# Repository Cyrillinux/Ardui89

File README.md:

#Ardui89 8051 C IDE 0.4.2 for Arduino IDE

#Under GPL license

Adds 8051 architecture family to the Arduino IDE :
STC89C52RC, STC89C516RD+, STC15W408AS-DIP16

* DISCLAIMER OF ALL WARRANTIES *

Allows you to COMPILE a .ino file of the 8051 C family program and UPLOAD it into the STC89C5x, STC15..., etc. family.

#Versions
0.0.1  : first Mac OS try (compiling only) (Arch 8051 STC89C51RC(4kb) and STC89C52RC(8kb))
0.0.6   : Mac OS completed (compiling and programming)
0.1.1   : tone function builtin, bugs fixed
0.2.0   : first windows try (compilling only)
0.2.1   : fist windows version completed (compilling and programming)
0.2.2   : Warning : new PINOUT for 805x Arduino equivalent and add STC32G12K128 = 8952 with 128k flash memory
0.2.3   : PINOUT fixed, bugs fixed. Variants STC15F2K32S2, STC32G12K128 fixed
0.3.0   : Replace stcflash by stcgal -> stc15 best process, add STC15W408AS-DIP16
0.3.1   : Bugs fixed
0.3.2   : Mini bugs fixed. Primary linux beta version ready : See dependencies packages installation.
0.3.3   : Mini bugs fixed. Speed uplaod bug fixed / choice speed upload menu added
0.3.7   : Add Serial.readString / Add push-pull output configuration for STC micro-controllers
0.3.8   : (25/04/25) Ardui89 Cinque-Uno replaced by Uno 5X, any bugs fixed
0.3.9   : (25/05/23) Any bugs fixed : compiling core problem on Mac OS Sequoia and Windows 11
0.3.10  : (25/05/27) Add int_to_string like function (same to_string but for int exclusively), and 8051/pgmspace.h 
0.3.11  : (25/05/31) add STC89C516RD+ (62464 bytes (64kb-internal isp)) and 22.1184 Mhz clock option
BETA 0.3.12 : (25/06/14) add #include <string.h> + Prévoir les STC15F2K16 et K32 et STC32G12k128.
0.4.0   : (25/07/27) better RAM management
0.4.1   : (25/10/16) add 29.4912 Mhz external and internal clock option
0.4.1.1 : (26/03/08) same 0.4.1, just UNO Cinque X Board Revision (R2)
0.4.2   : (26/05/16) analogRead and analogPin functions add for STC15 / pwd/tone compute modifed, based on F_CPU (not only 11059200Mhz) / new programme size compute.
    analogPin(A0) or pinMode(A0,INPUT_ANALOG) / analogRead(A0)

#Platforms
MacOS, Wind'Oz. (Stable)

#To do
analogRead, analogWrite with ST15 and ST32 series.
Stable Linux version.

#Installation and test

1/ Donwload Arduino >= V1.8.19 

2/ Launch Arduino

3/ In Arduino->Preferences->Additional Board Manager URLS
    add for Arduino All Versions
    https://master.dl.sourceforge.net/project/stc89/packages/package_ardui89_index.json?viasf=1
    
4/ In Tools->Boards:...->Board Manager
    search "8051"
    select and install "ardui89 8051 family Boards"
    
5/ In Tools->Board:...
    select "Board : "STC89C52RC" "STC89C516RD+" "STC15W408AS-DIP16""
    
6/ Demos :
    Use Blink.ino in basics examples or in Ardui89_demos path :
    Hello.ino
    Howareyou.ino
    
    and build and upload !

#Linux Dependencies

python3 / python3-pip / stcgal / sdcc

Under terminal :

1/ Installing stcgal :

sudo apt-get install python3 python3-pip

sudo python3 -m pip stcgal

2/ Installing SDCC :

sudo apt-get install sdcc

#Important

Under Wind'Oz, using absoluty last version (>=3.8) of CH340 drivers (CH341SER.ZIP) (Included in this package).

Many thanks

Cyril BARBATO

https://sourceforge.net/projects/stc89
cyril.barbato@gmx.com

# Arduino <=> STC89C51/STC89C52/STC89C5x/STC89C51x pinout equivalent
(Ardui89 Cinque Uno/Due/128k R0)

D : Arduino digital pins
A : Arduino analog pins
LED_BULTIN : D13 (P3.5)

 D                                                                 D  A
               +---------------\/--------------+
               |                               |
 7 P1.0 -------|  1  P1.0              VCC  40 |------ VCC
 8 P1.1 -------|  2  P1.1             P0.0  39 |------ P0.0 (AD0) 31 A7
 2 P1.2 -------|  3  P1.2             P0.1  38 |------ P0.1 (AD1) 30 A6
 3 P1.3 -------|  4  P1.3             P0.2  37 |------ P0.2 (AD2) 29 A5 SCL
 4 P1.4 -------|  5  P1.4             P0.3  36 |------ P0.3 (AD3) 28 A4 SDA
 5 P1.5 (MOSI)-|  6  P1.5 (MOSI)      P0.4  35 |------ P0.4 (AD4) 27 A3
 6 P1.6 (MISO)-|  7  P1.6 (MISO)      P0.5  34 |------ P0.5 (AD5) 26 A2
 7 P1.7 (SCK)--|  8  P1.7 (SCK)       P0.6  33 |------ P0.6 (AD6) 25 A1
    RST -------|  9  RST              P0.7  32 |------ P0.7 (AD7) 24 A0
 0 P3.0 -------| 10  P3.0 (RXD)   (VPP) EA  31 |------ EA   (VPP)
 1 P3.1 -------| 11  P3.1 (TXD)  (PRG) ALE  30 |------ ALE  (PRG)
10 P3.2 -------| 12  P3.2 (INT0)     /PSEN  29 |------ /PSEN
11 P3.3 -------| 13  P3.3 (INT1)      P2.7  28 |------ P2.7 (A15) 23
12 P3.4 -------| 14  P3.4 (T0)        P2.6  27 |------ P2.6 (A14) 22
13 P3.5 -------| 15  P3.5 (T1)        P2.5  26 |------ P2.5 (A13) 21
14 P3.6 -------| 16  P3.6 (WR)        P2.4  25 |------ P2.4 (A12) 20
15 P3.7 -------| 17  P3.7 (RD)        P2.3  24 |------ P2.3 (A11) 19
  XTAL2 -------| 18  XTAL2            P2.2  23 |------ P2.2 (A10) 18
  XTAL1 -------| 19  XTAL1 P          P2.1  22 |------ P2.1 (A9)  17
    GND -------| 20  GND              P2.0  21 |------ P2.0 (A8)  16
               +-------------------------------+

# Arduino <=> STC15W408AS-DIP28 / STC15F2K16 or 32 pinout equivalent
(Ardui89 UNO R0)

D : Arduino digital pins
A : Arduino analog pins
LED_BULTIN : D13 (P2.5)
SDA : A4 (D22/P1.4)
SCL : A5 (D23/P1.5)

A   D                                                                         D
                  +---------------------\_/--------------------+
   14 P2.6 -------|  1 P2.6 (CCP1)            (CCP0_3) P2.5 28 |------- P2.5 13
   15 P2.7 -------|  2 P2.7 (CCP2)             (ECI_3) P2.4 27 |------- P2.4 12
A0 18 P1.0 -------|  3 P1.0 (RxD2)            (MOSI_2) P2.3 26 |------- P2.3 11
A1 19 P1.1 -------|  4 P1.1 (TxD2)            (MISO_2) P2.2 25 |------- P2.2 10
A2 20 P1.2 -------|  5 P1.2 (ECI)             (SCLK_2) P2.1 24 |------- P2.1  9
A3 21 P1.3 -------|  6 P1.3 (MOSI)        (RSTOUT_LOW) P2.0 23 |------- P2.0  8
A4 22 P1.4 -------|  7 P1.4 (MISO) (INT3/TxD_2/CCP2_2) P3.7 22 |------- P3.7  7
A5 23 P1.5 -------|  8 P1.5 (SCLK)  (NT2/RxD_2/CCP1_2) P3.6 21 |------- P3.6  6
       XT2 -------|  9 P1.6 (XTAL2) (T1/T0CLKO/CCP0_2) P3.5 20 |------- P3.5  5
       XT1 -------| 10 P1.7 (XTAL1)  (T0/T1CLKO/ECI_2) P3.4 19 |------- P3.4  4
   16  RST -------| 11 P5.4 (MCLKO)             (INT1) P3.3 18 |------- P3.3  3
       Vcc -------| 12 Vcc                      (INT0) P3.2 17 |------- P3.2  2
   17 P5.5 -------| 13 P5.5                   (TxD/T2) P3.1 16 |------- P3.1  1
      Gnd  -------| 14  Gnd          (RxD/INT4/T2CLKO) P3.0 15 |------- P3.0  0
                  +--------------------------------------------+

# Arduino <=> STC15W408AS-DIP16
(Ardui89 MINI R0)

D : Arduino digital pins
A : Arduino analog pins
LED_BULTIN : D7 (P3.7)
SDA : A4 (D12/P1.4)
SCL : A5 (D13/P1.5)

 D   A                                                                 A D
                   +-----------------\_/----------------+
 10 A2 P1.2 -------| 1 P1.2                     P1.1 16 |------- P1.1 A1 9
 11 A3 P1.3 -------| 2 P1.3 (MOSI)              P1.0 15 |------- P1.0 A0 8
 12 A4 P1.4 -------| 3 P1.4 (MISO) (/INT3-TxD2) P3.7 14 |------- P3.7    7
 13 A5 P1.5 -------| 4 P1.5 (SLK)  (/INT2-RxD2) P3.6 13 |------- P3.6    6
  4    P5.4 -------| 5 P5.4              (INT1) P3.3 12 |------- P3.3    3
        Vcc -------| 6 Vcc               (INT0) P3.2 11 |------- P3.2    2
  5    P5.5 -------| 7 P5.5               (TxD) P3.1 10 |------- P3.1    1
        Gnd -------| 8 Gnd                (RxD) P3.0  9 |------- P3.0    0
                   +------------------------------------+

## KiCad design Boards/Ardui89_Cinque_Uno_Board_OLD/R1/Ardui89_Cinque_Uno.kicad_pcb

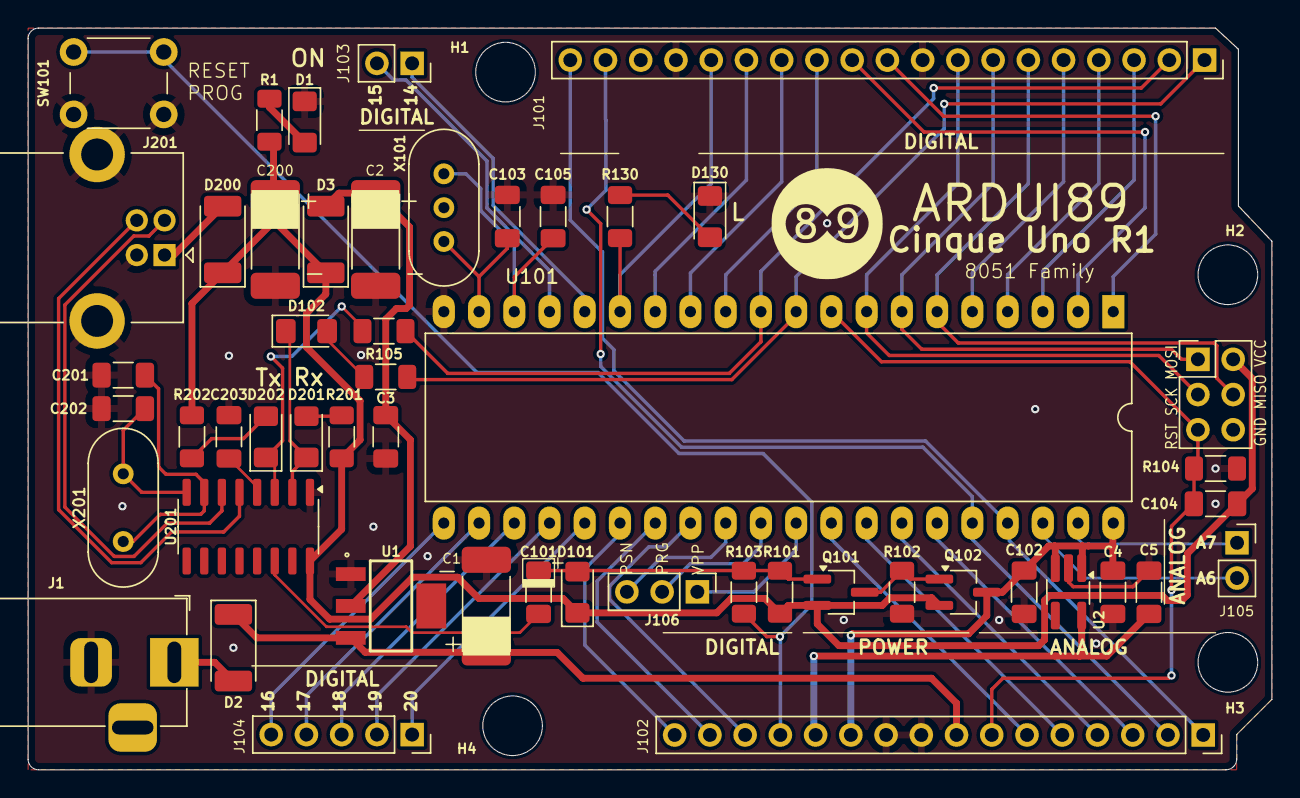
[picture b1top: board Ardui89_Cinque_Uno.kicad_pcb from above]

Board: 2 copper layers, 89.7 x 53.5 mm, 55 parts (0 on the bottom side), 62 nets.

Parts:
C1, C2, C200: 10µ; C_2512_Pol_Tantale_Trainning
C3, C4, C5, C102, C104, C203: 100n; C_1206_3216Metric_Pad1.33x1.80mm_HandSolder
C101: 10µ; C_1206_POL_3216Metric_Pad1.33x1.80mm_HandSolder
C103, C105: 22p; C_1206_3216Metric_Pad1.33x1.80mm_HandSolder
C201, C202: 27p; C_1206_3216Metric_Pad1.33x1.80mm_HandSolder
D1: LED; D_1206_3216Metric_Pad1.42x1.75mm_HandSolder
D2, D3, D200: SM34; D_MELF
D101, D102: 1N5819W; D_1206_3216Metric_Pad1.42x1.75mm_HandSolder
D130: BUILTIN_LED; D_1206_3216Metric_Pad1.42x1.75mm_HandSolder
D201: Rx LED; D_1206_3216Metric_Pad1.42x1.75mm_HandSolder
D202: Tx LED; D_1206_3216Metric_Pad1.42x1.75mm_HandSolder
H1: Mounting Hole 4.3mm; MountingHole_4.3mm_M4_DIN965
H2, H3, H4: MountingHole; MountingHole_4.3mm_M4_DIN965
ICSP101: M20-9980346; PinHeader_2x03_P2.54mm_Vertical
J1: Jack-DC; BarrelJack_Horizontal
J101: Conn_01x19; Ardu89_Uno_Digital_Connector
J102: Conn_01x16; Ardu89_Uno_Analog_Power_Connector
J103, J105: Extented Port; PinSocket_1x02_P2.54mm_Vertical
J104: Extended Port; PinSocket_1x05_P2.54mm_Vertical
J106: Conn_01x03; PinHeader_1x03_P2.54mm_Vertical
J201: USB_TYPE_B; USB_B_Lumberg_2411_02_Horizontal
Q101, Q102: MMBTA2907; TSOT-23_HandSoldering
R1, R101, R103, R104, R130, R201, R202: 1k; R_1206_3216Metric_Pad1.30x1.75mm_HandSolder
R102: 4k7; R_1206_3216Metric_Pad1.30x1.75mm_HandSolder
R105, R106: 330; R_1206_3216Metric_Pad1.30x1.75mm_HandSolder
SW101: SW_Push; SW_PUSH_6mm
U1: LD1117S50TR; SOT230P700X180-4N
U2: LP2985-33DBVR; TSOT-23-5_HandSoldering
U101: 89C5x; DIP-40_W15.24mm_LongPads
U201: CH340G; SOIC-16_3.9x9.9mm_P1.27mm
X101: 11.0592MHz; Crystal_HC49-U-3PinB_Vertical
X201: 12MHz; Crystal_HC49-4H_Vertical

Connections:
/3.3V: C5.1, J102.12, U2.5 (VOUT)
/A0: J102.6, U101.32 (P0.7_(AD7))
/A1: J102.5, U101.33 (P0.6_(AD6))
/A2: J102.4, U101.34 (P0.5_(AD5))
/A3: J102.3, U101.35 (P0.4_(AD4))
/A4_SDA: J101.18, J102.2, U101.36 (P0.3_(AD3))
/A5_SCL: J101.19, J102.1, U101.37 (P0.2_(AD2))
/A6: J105.2, U101.38 (P0.1_(AD1))
/A7: J105.1, U101.39 (P0.0_(AD0))
/D0: J101.1, R105.1, U101.10 ((RXD)_P3.0)
/D1: J101.2, R106.1, U101.11 ((TXD)_P3.1)
/D2: J101.3, U101.3 (P1.2)
/D3: J101.4, U101.4 (P1.3)
/D4: J101.5, U101.5 (P1.4)
/D5: ICSP101.4, J101.6, U101.6 ((MOSI)_P1.5)
/D6: ICSP101.1, J101.7, U101.7 ((MISO)_P1.6)
/D7: ICSP101.3, J101.8, U101.8 ((SCK)_P1.7)
/D8: J101.10, U101.1 ((T2)_P1.0)
/D9: J101.11, U101.2 ((T2_EX)_P1.1)
/D10: J101.12, U101.12 ((INT0)_P3.2)
/D11: J101.13, U101.13 ((INT1)_P3.3)
/D12: J101.14, U101.14 ((T0)_P3.4)
/D13: J101.15, R130.2, U101.15 ((T1)_P3.5)
/D14: J103.1, U101.16 ((WR)_P3.6)
/D15: J103.2, U101.17 ((RD)_P3.7)
/D16: J104.5, U101.21 (P2.0_(A8))
/D17: J104.4, U101.22 (P2.1_(A9))
/D18: J104.3, U101.23 (P2.2_(A10))
/D19: J104.2, U101.24 (P2.3_(A11))
/D20: J104.1, U101.25 (P2.4_(A12))
/D21: J102.16, U101.26 (P2.5_(A13))
/D22: J102.15, U101.27 (P2.6_(A14))
/D23: J102.14, U101.28 (P2.7_(A15))
/D+: J201.3 (D+), U201.5 (UD+)
/D-: J201.2 (D-), U201.6 (UD-)
/RESET: C104.2, ICSP101.5, J102.7, R104.2, U101.9 (RST)
/RTS: C101.2, U201.14 (~RTS)
/Rx: D102.1 (K), D201.1 (K), U201.2 (TXD)
/Tx: D202.1 (K), R106.2, U201.3 (RXD)
/Vin: C1.1, D2.1 (K), J102.8, U1.3 (Vin)
//RST: J102.13, R103.1, SW101.2
GND: C1.2, C2.2, C3.2, C4.2, C5.2, C102.2, C103.2, C105.2, C200.2, C201.2, C202.2, C203.2, D1.1 (K), D130.1 (K), ICSP101.6, J1.2, J101.9, J101.16, J102.9, J102.10, J201.4 (GND), J201.5 (Shield_1), R102.2, R104.1, SW101.1, U1.1 (GND), U2.2 (GND), U101.20 (GND), U201.1 (GND)
unnamed: D1.2 (A), R1.2
unnamed: D2.2 (A), J1.1
unnamed: C2.1, C3.1, D3.2 (A), U1.2 (Vout)
unnamed: C101.1, D101.2 (A), Q101.1 (B), R101.2, R103.2
unnamed: D102.2 (A), R105.2
unnamed: D130.2 (A), R130.1
unnamed: D200.2 (A), J201.1 (Vbus)
unnamed: D201.2 (A), R201.2
unnamed: D202.2 (A), R202.2
unnamed: J106.1, U101.31 (~EA/VPP)
unnamed: J106.2, U101.30 (ALE/~PROG)
unnamed: J106.3, U101.29 (~PSEN)
unnamed: Q101.3 (C), Q102.1 (B), R102.1
unnamed: C103.1, U101.19 (XTAL1), X101.2
unnamed: C105.1, U101.18 (XTAL2), X101.1
unnamed: C203.1, U201.4 (V3)
unnamed: C201.1, U201.7 (XI), X201.2
unnamed: C202.1, U201.8 (XO), X201.1
VCC: C104.1, C200.1, D3.1 (K), D101.1 (K), D200.1 (K), ICSP101.2, Q101.2 (E), Q102.2 (E), R1.1, R101.1, R201.1, R202.1, U201.16 (VCC)
VCPU: C4.1, C102.1, J102.11, Q102.3 (C), U2.1 (VIN), U2.3 (ON/~OFF), U101.40 (VCC)

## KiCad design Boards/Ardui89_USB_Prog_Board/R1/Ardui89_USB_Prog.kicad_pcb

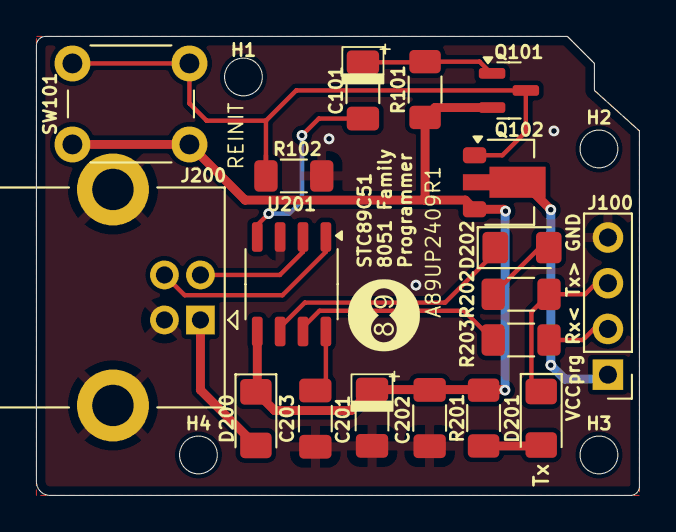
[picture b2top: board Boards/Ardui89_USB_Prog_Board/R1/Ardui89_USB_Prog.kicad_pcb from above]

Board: 2 copper layers, 33.5 x 25.5 mm, 22 parts (0 on the bottom side), 16 nets.

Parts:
C101, C201: 10µ; C_1206_POL_3216Metric_Pad1.33x1.80mm_HandSolder
C202, C203: 100n; C_1206_3216Metric_Pad1.33x1.80mm_HandSolder
D200, D202: 1N5819W; D_1206_3216Metric_Pad1.42x1.75mm_HandSolder
D201: Tx LED; D_1206_3216Metric_Pad1.42x1.75mm_HandSolder
H1, H2, H3, H4: MountingHole; MountingHole_2.1mm
J100: Conn_01x04; PinHeader_1x04_P2.54mm_Vertical
J200: USB_TYPE_B; USB_B_Lumberg_2411_02_Horizontal
Q101: SI2301; SOT-23
Q102: BCX51; SOT-89-3
R101: 20k; R_1206_3216Metric_Pad1.30x1.75mm_HandSolder
R102: 4k7; R_1206_3216Metric_Pad1.30x1.75mm_HandSolder
R201: 1k; R_1206_3216Metric_Pad1.30x1.75mm_HandSolder
R202, R203: 330; R_1206_3216Metric_Pad1.30x1.75mm_HandSolder
SW101: SW_Push; SW_PUSH_6mm
U201: CH340N; SOP-8_3.9x4.9mm_P1.27mm

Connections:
/D+: J200.3 (D+), U201.1 (UD+)
/D-: J200.2 (D-), U201.2 (UD-)
/Rx: J100.2, R203.1
/Tx: D201.1 (K), J100.3, R202.1
//RTS: C101.2, U201.4 (~RTS)
GND: C201.2, C202.2, C203.2, J100.4, J200.4 (GND), J200.5 (Shield_1), R102.2, U201.3 (GND)
unnamed: D200.2 (A), J200.1 (Vbus)
unnamed: D201.2 (A), R201.2
unnamed: D202.2 (A), R202.2
unnamed: D202.1 (K), U201.6 (TXD)
unnamed: J100.1, Q102.2 (C)
unnamed: Q101.3 (D), Q102.1 (B), R102.1, SW101.2
unnamed: C101.1, Q101.1 (G), R101.2
unnamed: R203.2, U201.7 (RXD)
unnamed: C203.1, U201.8 (V3)
VCC: C201.1, C202.1, D200.1 (K), Q101.2 (S), Q102.3 (E), R101.1, R201.1, SW101.1, U201.5 (VCC)

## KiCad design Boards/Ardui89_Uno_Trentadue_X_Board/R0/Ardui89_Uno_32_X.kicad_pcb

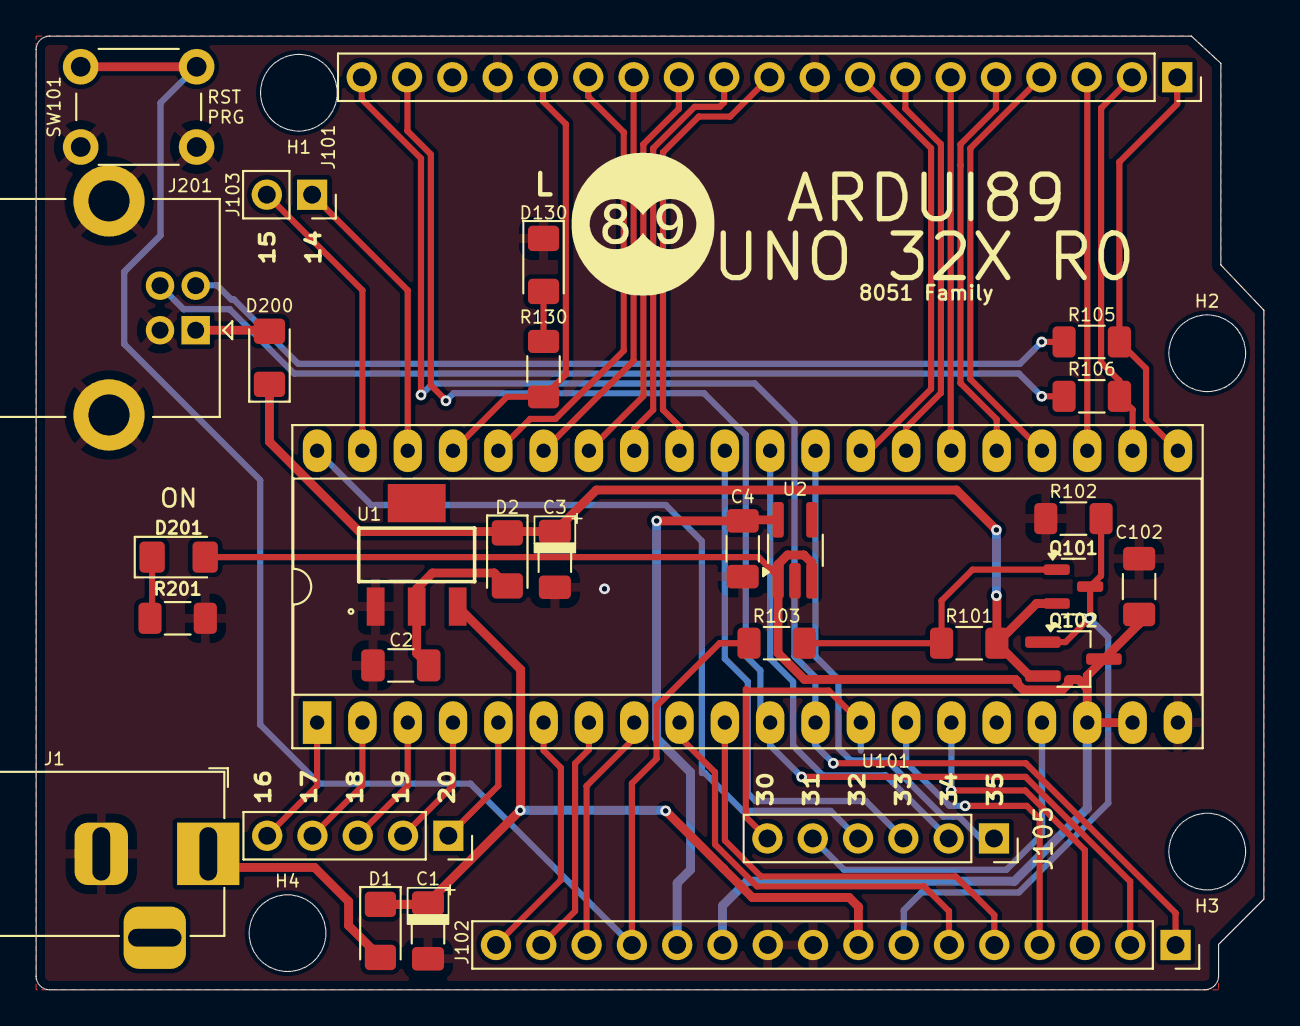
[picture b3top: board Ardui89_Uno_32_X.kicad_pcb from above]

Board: 2 copper layers, 68.8 x 53.5 mm, 34 parts (0 on the bottom side), 51 nets.

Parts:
C1, C3: 10µ; C_1206_POL_3216Metric_Pad1.33x1.80mm_HandSolder
C2, C4, C102: 100n; C_1206_3216Metric_Pad1.33x1.80mm_HandSolder
D1, D2, D200: 1N5819W; D_1206_3216Metric_Pad1.42x1.75mm_HandSolder
D130: BUILTIN_LED; D_1206_3216Metric_Pad1.42x1.75mm_HandSolder
D201: ON LED; D_1206_3216Metric_Pad1.42x1.75mm_HandSolder
H1: Mounting Hole 4.3mm; MountingHole_4.3mm_M4_DIN965
H2, H3, H4: MountingHole; MountingHole_4.3mm_M4_DIN965
J1: Jack-DC; BarrelJack_Horizontal
J101: Conn_01x19; Ardu89_Uno_Digital_Connector
J102: Conn_01x16; Ardu89_Uno_Analog_Power_Connector
J103: Extented Port; PinSocket_1x02_P2.54mm_Vertical
J104: Extended Port; PinSocket_1x05_P2.54mm_Vertical
J105: Conn_01x06; PinSocket_1x06_P2.54mm_Vertical
J201: USB_TYPE_B; USB_B_Lumberg_2411_02_Horizontal
Q101: SI2301; SOT-23
Q102: MMBTA2907; TSOT-23_HandSoldering
R101, R130: 1k; R_1206_3216Metric_Pad1.30x1.75mm_HandSolder
R102: 4k7; R_1206_3216Metric_Pad1.30x1.75mm_HandSolder
R103: 330; R_1206_3216Metric_Pad1.30x1.75mm_HandSolder
R105, R106: 33; R_1206_3216Metric_Pad1.30x1.75mm_HandSolder
R201: 2k2; R_1206_3216Metric_Pad1.30x1.75mm_HandSolder
SW101: SW_Push; SW_PUSH_6mm
U1: LD1117S50TR; SOT230P700X180-4N
U2: LP2985-33DBVR; TSOT-23-5_HandSoldering
U101: STC32G12K128; DIP-40_W15.24mm_Socket_LongPads

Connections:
/3.3V: C4.1, J102.12, U2.5 (VOUT)
/D0: J101.1, R105.1, U101.21 ((D0)_D-/P3.0)
/D1: J101.2, R106.1, U101.22 ((D1)_D+/P3.1)
/D2: J101.3, U101.23 (P3.2)
/D3: J101.4, U101.24 (P3.3)
/D4: J101.5, U101.25 (P3.4)
/D5: J101.6, U101.26 (P3.5)
/D6: J101.7, U101.27 (P3.6)
/D7: J101.8, U101.28 (P3.7)
/D8: J101.10, U101.32 (P2.0)
/D9: J101.11, U101.33 (P2.1)
/D10_SS: J101.12, U101.34 (P2.2)
/D11_MOSI: J101.13, U101.35 (P2.3)
/D12_MISO: J101.14, U101.36 (P2.4)
/D13_SCK: J101.15, R130.2, U101.37 (P2.5)
/D14: J103.1, U101.38 (P2.6)
/D15: J103.2, U101.39 (P2.7)
/D16: J104.5, U101.1 (P0.0)
/D17: J104.4, U101.2 (P0.1)
/D18: J104.3, U101.3 (P0.2)
/D19: J104.2, U101.4 (P0.3)
/D20: J104.1, U101.5 (P0.4)
/D21: J102.16, U101.6 (P0.5)
/D22: J102.15, U101.7 (P0.6)
/D23: J102.14, U101.8 (P0.7)
/D24_A0: J102.6, U101.9 (P1.0)
/D25_A1: J102.5, U101.10 (P1.1)
/D26_A2: J102.4, U101.14 (P1.7)
/D27_A3: J102.3, U101.15 (P1.3)
/D28_A4_SDA: J101.18, J102.2, U101.11 (P1.4)
/D29_A5_SCL: J101.19, J102.1, U101.12 (P1.5)
/D30_A6: J105.6, U101.13 (P1.6)
/D31: J105.5, U101.17 (P5.4)
/D32: J105.4, U101.40 (P4.5)
/D33: J105.3, U101.31 (P4.4)
/D34: J105.2, U101.30 (P4.2)
/D35: J105.1, U101.29 (P4.1)
/D+: J201.3 (D+), R106.2
/D-: J201.2 (D-), R105.2
/RESET: J102.7, Q101.3 (D), Q102.1 (B), R102.1
/Vin: C1.1, D1.1 (K), J102.8, U1.3 (Vin)
//RST: J102.13, R103.1, SW101.2
GND: C1.2, C2.2, C3.2, C4.2, C102.2, D130.1 (K), J1.2, J101.9, J101.16, J102.9, J102.10, J201.4 (GND), J201.5 (Shield_1), R102.2, R201.1, SW101.1, U1.1 (GND), U2.2 (GND), U101.20 (GND)
unnamed: D1.2 (A), J1.1
unnamed: C2.1, D2.2 (A), U1.2 (Vout)
unnamed: D130.2 (A), R130.1
unnamed: D200.2 (A), J201.1 (Vbus)
unnamed: D201.1 (K), R201.2
unnamed: Q101.1 (G), R101.2, R103.2
VCC: C3.1, D2.1 (K), D200.1 (K), Q101.2 (S), Q102.2 (E), R101.1
VCPU: C102.1, D201.2 (A), J102.11, Q102.3 (C), U2.1 (VIN), U2.3 (ON/~OFF), U101.18 (VCC), U101.19 (Vref)

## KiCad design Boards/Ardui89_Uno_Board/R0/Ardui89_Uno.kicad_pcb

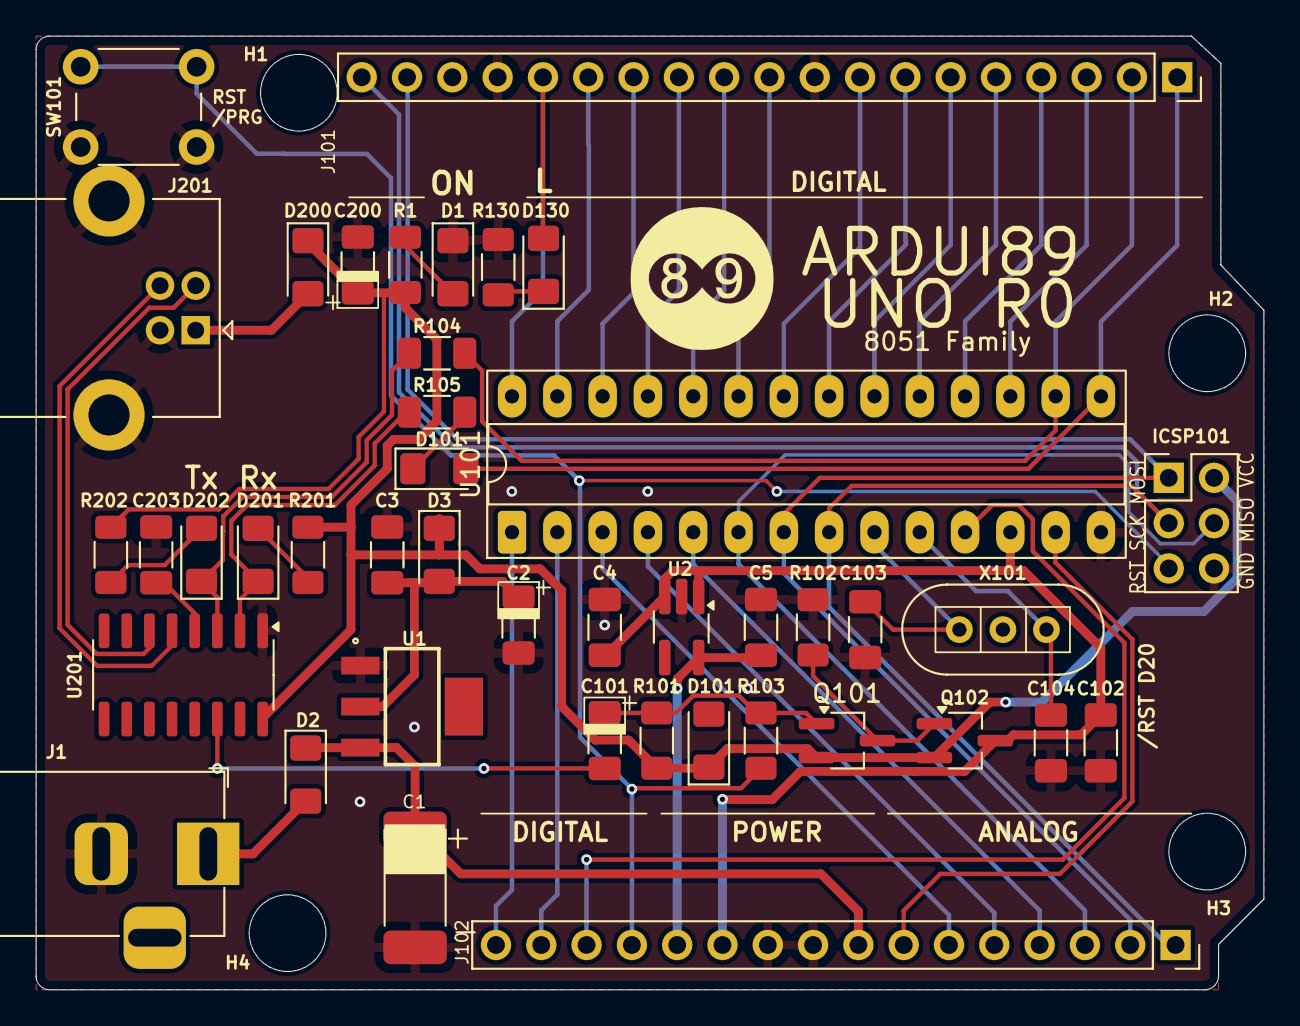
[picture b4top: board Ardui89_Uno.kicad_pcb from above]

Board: 2 copper layers, 68.8 x 53.5 mm, 46 parts (0 on the bottom side), 48 nets.

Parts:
C1: 10uF; C_2512_Pol_Tantale_Trainning
C2: 10µf; C_1206_POL_3216Metric_Pad1.33x1.80mm_HandSolder
C3, C4, C5, C102, C203: 100n; C_1206_3216Metric_Pad1.33x1.80mm_HandSolder
C101, C200: 10µ; C_1206_POL_3216Metric_Pad1.33x1.80mm_HandSolder
C103, C104: 22p; C_1206_3216Metric_Pad1.33x1.80mm_HandSolder
D1: LED 'ON'/Red; D_1206_3216Metric_Pad1.42x1.75mm_HandSolder
D2, D3, D101, D101#2, D200: 1N5819W; D_1206_3216Metric_Pad1.42x1.75mm_HandSolder
D130: LED BUILTIN/Blue; D_1206_3216Metric_Pad1.42x1.75mm_HandSolder
D201: Rx LED/Orange; D_1206_3216Metric_Pad1.42x1.75mm_HandSolder
D202: Tx LED/Orange; D_1206_3216Metric_Pad1.42x1.75mm_HandSolder
H1: Mounting Hole 4.3mm; MountingHole_4.3mm_M4_DIN965
H2, H3, H4: MountingHole; MountingHole_4.3mm_M4_DIN965
ICSP101: M20-9980346; PinHeader_2x03_P2.54mm_Vertical
J1: Barrel Jack; BarrelJack_Horizontal
J101: Conn_01x19; Ardu89_Uno_Digital_Connector
J102: Conn_01x16; Ardu89_Uno_Analog_Power_Connector
J201: USB_TYPE_B; USB_B_Lumberg_2411_02_Horizontal
Q101: SI2301; TSOT-23_HandSoldering
Q102: MMBT2907; TSOT-23_HandSoldering
R1: 2k2; R_1206_3216Metric_Pad1.30x1.75mm_HandSolder
R101: 20k; R_1206_3216Metric_Pad1.30x1.75mm_HandSolder
R102: 4k7; R_1206_3216Metric_Pad1.30x1.75mm_HandSolder
R103, R130, R201, R202: 1k; R_1206_3216Metric_Pad1.30x1.75mm_HandSolder
R104, R105: 1K; R_1206_3216Metric_Pad1.30x1.75mm_HandSolder
SW101: SW_Push; SW_PUSH_6mm
U1: LD1117S50TR; SOT230P700X180-4N
U2: LP2985-33DBVR; TSOT-23-5_HandSoldering
U101: STC15F2K16/32-DIP28; DIP-28_W7.62mm_Socket_LongPads
U201: CH340C; SOIC-16_3.9x9.9mm_P1.27mm
X101: =>11.0592MHz; Crystal_HC49-U-3PinB_Vertical_Socket

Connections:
/3.3V: C5.1, J102.12, U2.5 (VOUT)
/A0: J102.6, U101.3 ((CCP1/ADC0)_P1.0)
/A1: J102.5, U101.4 ((CCP0/ADC1)_P1.1)
/A2: J102.4, U101.5 ((CMP0/ECI/SS/ADC2)_P1.2)
/A3: ICSP101.4, J102.3, U101.6 ((MOSI/ADC3)_P1.3)
/A4_SDA: ICSP101.1, J101.18, J102.2, U101.7 ((MISO/ADC4)_P1.4)
/A5_SCL: ICSP101.3, J101.19, J102.1, U101.8 ((SCLK/ADC5)_P1.5)
/D0: D101.2 (A), J101.1, U101.15 ((RxD/_INT4)_P3.0)
/D1: J101.2, R104.1, U101.16 ((TxD/T2)_P3.1)
/D2: J101.3, U101.17 ((INT0)_P3.2)
/D3: J101.4, U101.18 ((INT1)_P3.3)
/D4: J101.5, U101.19 ((ECI2/T0)_P3.4)
/D5: J101.6, U101.20 ((T0CLK0/CCP02)_P3.5)
/D6: J101.7, U101.21 ((RxD2/_INT2/CCP12)_P3.6)
/D7: J101.8, U101.22 ((TxD2/_INT3/CCP22)_P3.7)
/D8: J101.10, U101.23 ((RSTOUT_LOW)_P2.0)
/D9: J101.11, U101.24 ((SCLK2)_P2.1)
/D10: J101.12, U101.25 ((MISO2)_P2.2)
/D11: J101.13, U101.26 ((MOSI2)_P2.3)
/D12: J101.14, U101.27 ((ECI3/SS2)_P2.4)
/D13: D130.2 (A), J101.15, U101.28 ((CCP03)_P2.5)
/D14: J102.16, U101.1 ((CCP13)_P2.6)
/D15: J102.15, U101.2 ((CCP23)_P2.7)
/D16_RST: J102.14, U101.11 ((RESET/CMP-/SyCK0)_P5.4)
/D17: J102.7, U101.13 ((CMP+)_P5.5)
/D+: J201.3 (D+), U201.5 (UD+)
/D-: J201.2 (D-), U201.6 (UD-)
/Rx: D201.1 (K), R105.2, U201.2 (TXD)
/Tx: D202.1 (K), R104.2, U201.3 (RXD)
/Vin: C1.1, D2.1 (K), J102.8, U1.3 (Vin)
//RST: ICSP101.5, J102.13, R103.2, SW101.2
//RTS: C101.2, U201.14 (~RTS)
GND: C1.2, C2.2, C3.2, C4.2, C5.2, C102.2, C103.2, C104.2, C200.2, C203.2, D1.1 (K), ICSP101.6, J1.2, J101.9, J101.16, J102.9, J102.10, J201.4 (GND), J201.5 (Shield_1), R102.2, R130.2, SW101.1, U1.1 (GND), U2.2 (GND), U101.14 (GND), U201.1 (GND)
unnamed: D1.2 (A), R1.2
unnamed: D2.2 (A), J1.1
unnamed: C2.1, C3.1, D3.2 (A), U1.2 (Vout)
unnamed: D101.1 (K), R105.1
unnamed: D130.1 (K), R130.1
unnamed: D200.2 (A), J201.1 (Vbus)
unnamed: D201.2 (A), R201.2
unnamed: D202.2 (A), R202.2
unnamed: Q101.3 (D), Q102.1 (B), R102.1
unnamed: C101.1, Q101.1 (G), R101.2, R103.1
unnamed: C104.1, U101.10 ((XT1/TxD3/ADC7)_P1.7), X101.1
unnamed: C103.1, U101.9 ((XT2/RxD3/ADC6)_P1.6), X101.2
unnamed: C203.1, U201.4 (V3)
VCC: C200.1, D3.1 (K), D101#2.1 (K), D200.1 (K), ICSP101.2, Q101.2 (S), Q102.2 (E), R1.1, R101.1, R201.1, R202.1, U201.16 (VCC)
VCPU: C4.1, C102.1, J102.11, Q102.3 (C), U2.1 (VIN), U2.3 (ON/~OFF), U101.12 (VCC)

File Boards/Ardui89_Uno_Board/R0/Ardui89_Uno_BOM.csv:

"Reference","Value","Footprint","Qty","#","Description"
"C1","10uF","BACKCIEL:C_2512_Pol_Tantale_Trainning","1","1","C_2512_Pol_Tantale/B/10µ/10V/Tantalum"
"C2","10µf","BACKCIEL:C_1206_POL_3216Metric_Pad1.33x1.80mm_HandSolder","1","2","C_1206_POL_3216Metric_Pad1.33x1.80mm/A/10µ/10V/Tantalum"
"C3,C4,C5,C102,C203","100n","Capacitor_SMD:C_1206_3216Metric_Pad1.33x1.80mm_HandSolder","5","3","C_1206_3216Metric_Pad1.33x1.80mm/Ceramic"
"C101,C200","10µ","BACKCIEL:C_1206_POL_3216Metric_Pad1.33x1.80mm_HandSolder","2","4","C_1206_POL_3216Metric_Pad1.33x1.80mm/A/10µ/10V/Tantalum"
"C103,C104","22p","Capacitor_SMD:C_1206_3216Metric_Pad1.33x1.80mm_HandSolder","2","5","C_1206_3216Metric_Pad1.33x1.80mm/Ceramic"
"D1","LED 'ON'/Red","Diode_SMD:D_1206_3216Metric_Pad1.42x1.75mm_HandSolder","1","6","D_1206_3216Metric_Pad1.42x1.75mm/Red"
"D2,D3,D101,D200","1N5819W","Diode_SMD:D_1206_3216Metric_Pad1.42x1.75mm_HandSolder","4","7","D_1206_3216Metric_Pad1.42x1.75mm"
"D130","LED BUILTIN/Blue","Diode_SMD:D_1206_3216Metric_Pad1.42x1.75mm_HandSolder","1","8","D_1206_3216Metric_Pad1.42x1.75mm/Blue"
"D201","Rx LED/Orange","Diode_SMD:D_1206_3216Metric_Pad1.42x1.75mm_HandSolder","1","9","D_1206_3216Metric_Pad1.42x1.75mm/Orange"
"D202","Tx LED/Orange","Diode_SMD:D_1206_3216Metric_Pad1.42x1.75mm_HandSolder","1","10","D_1206_3216Metric_Pad1.42x1.75mm/Orange"
"ICSP101","M20-9980346","Connector_PinHeader_2.54mm:PinHeader_2x03_P2.54mm_Vertical","1","11","CSP Header"
"J1","Barrel Jack","Connector_BarrelJack:BarrelJack_Horizontal","1","12","BarrelJack_Horizontal_5.5mmx2.1mm"
"J101","Conn_01x19","BACKCIEL:Ardu89_Uno_Digital_Connector","1","13","Generic connector, single row, 01x19, script generated (kicad-library-utils/schlib/autogen/connector/)"
"J102","Conn_01x16","BACKCIEL:Ardu89_Uno_Analog_Power_Connector","1","14","Generic connector, single row, 01x16, script generated (kicad-library-utils/schlib/autogen/connector/)"
"J201","USB_TYPE_B","Connector_USB:USB_B_Lumberg_2411_02_Horizontal","1","15","USB Type-B Connector"
"Q101","SI2301","Package_TO_SOT_SMD:TSOT-23_HandSoldering","1","16","SI2301"
"Q102","MMBT2907","Package_TO_SOT_SMD:TSOT-23_HandSoldering","1","17","MMBT2907"
"R1","2k2","Resistor_SMD:R_1206_3216Metric_Pad1.30x1.75mm_HandSolder","1","18","R_1206_3216Metric_Pad1.30x1.75mm"
"R101","20k","Resistor_SMD:R_1206_3216Metric_Pad1.30x1.75mm_HandSolder","1","19","R_1206_3216Metric_Pad1.30x1.75mm"
"R102","4k7","Resistor_SMD:R_1206_3216Metric_Pad1.30x1.75mm_HandSolder","1","20","R_1206_3216Metric_Pad1.30x1.75mm"
"R103,R130,R201,R202","1k","Resistor_SMD:R_1206_3216Metric_Pad1.30x1.75mm_HandSolder","4","21","R_1206_3216Metric_Pad1.30x1.75mm"
"R104,R105","1K","Resistor_SMD:R_1206_3216Metric_Pad1.30x1.75mm_HandSolder","2","22","R_1206_3216Metric_Pad1.30x1.75mm"
"SW101","SW_Push","Button_Switch_THT:SW_PUSH_6mm","1","23","Push button switch, generic, 4 pins/6mmx6mmx5mm"
"U1","LD1117S50TR","PRJ:SOT230P700X180-4N","1","24","5V Fixed LDO"
"U2","LP2985-33DBVR","Package_TO_SOT_SMD:TSOT-23-5_HandSoldering","1","25","3V3 Fixed LDO Regulator"
"U101","STC15W408AS-DIP16","Package_DIP:DIP-28_W7.62mm_Socket_LongPads","1","26","STC15W408AS-DIP28 on DIP-28 Tulip Socket / Not mounted directly"
"U201","CH340C","Package_SO:SOIC-16_3.9x9.9mm_P1.27mm","1","27",""
"X101","=>11.0592MHz","PRJLIB:Crystal_HC49-U-3PinB_Vertical_Socket","1","28",""

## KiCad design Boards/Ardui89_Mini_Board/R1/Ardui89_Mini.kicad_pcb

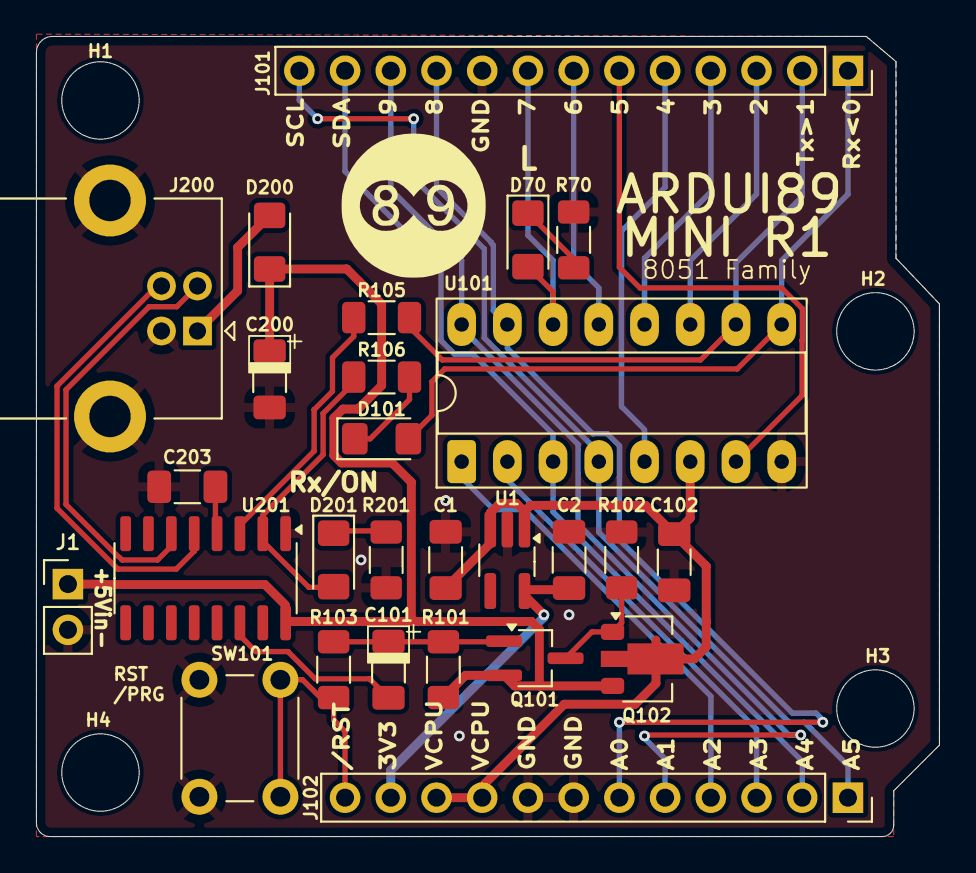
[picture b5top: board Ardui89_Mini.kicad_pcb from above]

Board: 2 copper layers, 50.2 x 44.5 mm, 31 parts (0 on the bottom side), 31 nets.

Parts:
C1, C2, C102, C203: 100n; C_1206_3216Metric_Pad1.33x1.80mm_HandSolder
C101, C200: 10µ; C_1206_POL_3216Metric_Pad1.33x1.80mm_HandSolder
D70: LED BUILTIN/Blue; D_1206_3216Metric_Pad1.42x1.75mm_HandSolder
D101, D200: 1N5819W; D_1206_3216Metric_Pad1.42x1.75mm_HandSolder
D201: /RxLED+ON/Orange; D_1206_3216Metric_Pad1.42x1.75mm_HandSolder
H1, H2, H3: MountingHole; MountingHole_4.3mm_M4_DIN965
H4: Mounting Hole 4.3mm; MountingHole_4.3mm_M4_DIN965
J1: Conn_01x02; PinHeader_1x02_P2.54mm_Vertical
J101: Conn_01x13; PinSocket_1x13_P2.54mm_Vertical
J102: Conn_01x12; PinSocket_1x12_P2.54mm_Vertical
J200: USB_TYPE_B; USB_B_Lumberg_2411_02_Horizontal
Q101: SI2301; TSOT-23_HandSoldering
Q102: BCX51; SOT-89-3
R70, R103, R201: 1k; R_1206_3216Metric_Pad1.30x1.75mm_HandSolder
R101: 20k; R_1206_3216Metric_Pad1.30x1.75mm_HandSolder
R102: 4k7; R_1206_3216Metric_Pad1.30x1.75mm_HandSolder
R105, R106: 330; R_1206_3216Metric_Pad1.30x1.75mm_HandSolder
SW101: SW_Push; SW_PUSH_6mm
U1: LP2985-33DBVR; TSOT-23-5_HandSoldering
U101: STC15W408AS-DIP16; DIP-16_W7.62mm_Socket_LongPads
U201: CH340C; SOIC-16_3.9x9.9mm_P1.27mm

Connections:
/3.3V: C2.1, J102.11, U1.5 (VOUT)
/A0_D8: J101.10, J102.6, U101.15 ((CCP1/ADC0)_P1.0)
/A1_D9: J101.11, J102.5, U101.16 ((CCP0/ADC1)_P1.1)
/A2: J102.4, U101.1 ((CMP0/ECI/SS/ADC2)_P1.2)
/A3: J102.3, U101.2 ((MOSI/ADC3)_P1.3)
/A4_SDA: J101.12, J102.2, U101.3 ((MISO/ADC4)_P1.4)
/A5_SCL: J101.13, J102.1, U101.4 ((SCLK/ADC5)_P1.5)
/D0: D101.2 (A), J101.1, U101.9 ((RxD/_INT4)_P3.0)
/D1: J101.2, R105.1, U101.10 ((TxD/T2)_P3.1)
/D2: J101.3, U101.11 ((INT0)_P3.2)
/D3: J101.4, U101.12 ((INT1)_P3.3)
/D4: J101.5, U101.5 ((RESET/CMP-/SyCK0)_P5.4)
/D5: J101.6, U101.7 ((CMP+)_P5.5)
/D6: J101.7, U101.13 ((RxD2/_INT2/CCP12)_P3.6)
/D7: D70.2 (A), J101.8, U101.14 ((TxD2/_INT3/CCP22)_P3.7)
/D+: J200.3 (D+), U201.5 (UD+)
/D-: J200.2 (D-), U201.6 (UD-)
/Rx: D201.2 (A), R106.2, U201.2 (TXD)
/Tx: R105.2, U201.3 (RXD)
//RST: J102.12, R103.2, SW101.1
//RTS: C101.2, U201.14 (~RTS)
GND: C1.2, C2.2, C102.2, C200.2, C203.2, J1.2, J101.9, J102.7, J102.8, J200.4 (GND), J200.5 (Shield_1), R70.2, R102.2, R201.2, SW101.2, U1.2 (GND), U101.8 (GND), U201.1 (GND)
unnamed: D70.1 (K), R70.1
unnamed: D101.1 (K), R106.1
unnamed: D200.2 (A), J200.1 (Vbus)
unnamed: D201.1 (K), R201.1
unnamed: Q101.3 (D), Q102.1 (B), R102.1
unnamed: C101.1, Q101.1 (G), R101.2, R103.1
unnamed: C203.1, U201.4 (V3)
VCC: C200.1, D200.1 (K), J1.1, Q101.2 (S), Q102.3 (E), R101.1, U201.16 (VCC)
VCPU: C1.1, C102.1, J102.9, J102.10, Q102.2 (C), U1.1 (VIN), U1.3 (ON/~OFF), U101.6 (VCC)

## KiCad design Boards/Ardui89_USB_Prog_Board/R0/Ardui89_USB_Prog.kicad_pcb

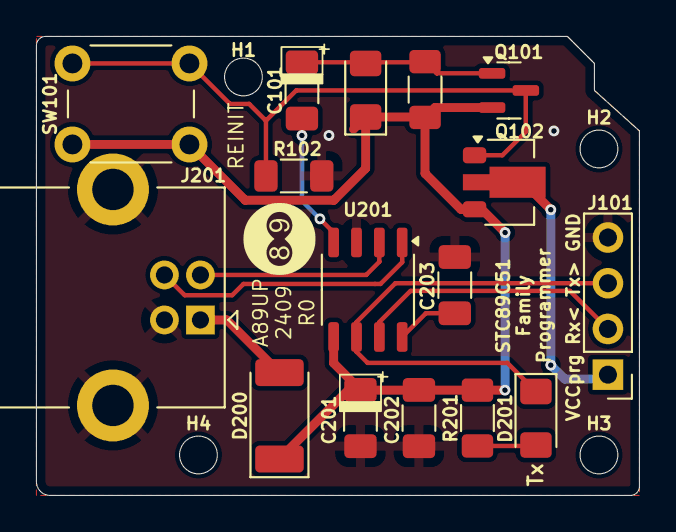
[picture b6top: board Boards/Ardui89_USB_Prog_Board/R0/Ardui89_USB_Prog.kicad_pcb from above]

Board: 2 copper layers, 33.5 x 25.5 mm, 20 parts (0 on the bottom side), 13 nets.

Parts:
C101, C201: 10µ; C_1206_POL_3216Metric_Pad1.33x1.80mm_HandSolder
C202, C203: 100n; C_1206_3216Metric_Pad1.33x1.80mm_HandSolder
D101: 1N5819W; D_1206_3216Metric_Pad1.42x1.75mm_HandSolder
D200: SM34; D_MELF
D201: Tx LED; D_1206_3216Metric_Pad1.42x1.75mm_HandSolder
H1, H2, H3, H4: MountingHole; MountingHole_2.1mm
J101: Conn_01x04; PinHeader_1x04_P2.54mm_Vertical
J201: USB_TYPE_B; USB_B_Lumberg_2411_02_Horizontal
Q101: SI2301; SOT-23
Q102: BCX51; SOT-89-3
R101, R201: 1k; R_1206_3216Metric_Pad1.30x1.75mm_HandSolder
R102: 4k7; R_1206_3216Metric_Pad1.30x1.75mm_HandSolder
SW101: SW_Push; SW_PUSH_6mm
U201: CH340N; SOP-8_3.9x4.9mm_P1.27mm

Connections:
/D+: J201.3 (D+), U201.1 (UD+)
/D-: J201.2 (D-), U201.2 (UD-)
/Rx: J101.2, U201.7 (RXD)
/Tx: D201.1 (K), J101.3, U201.6 (TXD)
//RTS: C101.2, U201.4 (~RTS)
GND: C201.2, C202.2, C203.2, J101.4, J201.4 (GND), J201.5 (Shield_1), R102.2, U201.3 (GND)
unnamed: C101.1, D101.2 (A), Q101.1 (G), R101.2
unnamed: D200.2 (A), J201.1 (Vbus)
unnamed: D201.2 (A), R201.2
unnamed: J101.1, Q102.2 (C)
unnamed: Q101.3 (D), Q102.1 (B), R102.1, SW101.2
unnamed: C203.1, U201.8 (V3)
VCC: C201.1, C202.1, D101.1 (K), D200.1 (K), Q101.2 (S), Q102.3 (E), R101.1, R201.1, SW101.1, U201.5 (VCC)

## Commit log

2024-07-08 Create makefile
2024-07-08 Update makefile
2026-05-16 Initial commit of Ardui89
